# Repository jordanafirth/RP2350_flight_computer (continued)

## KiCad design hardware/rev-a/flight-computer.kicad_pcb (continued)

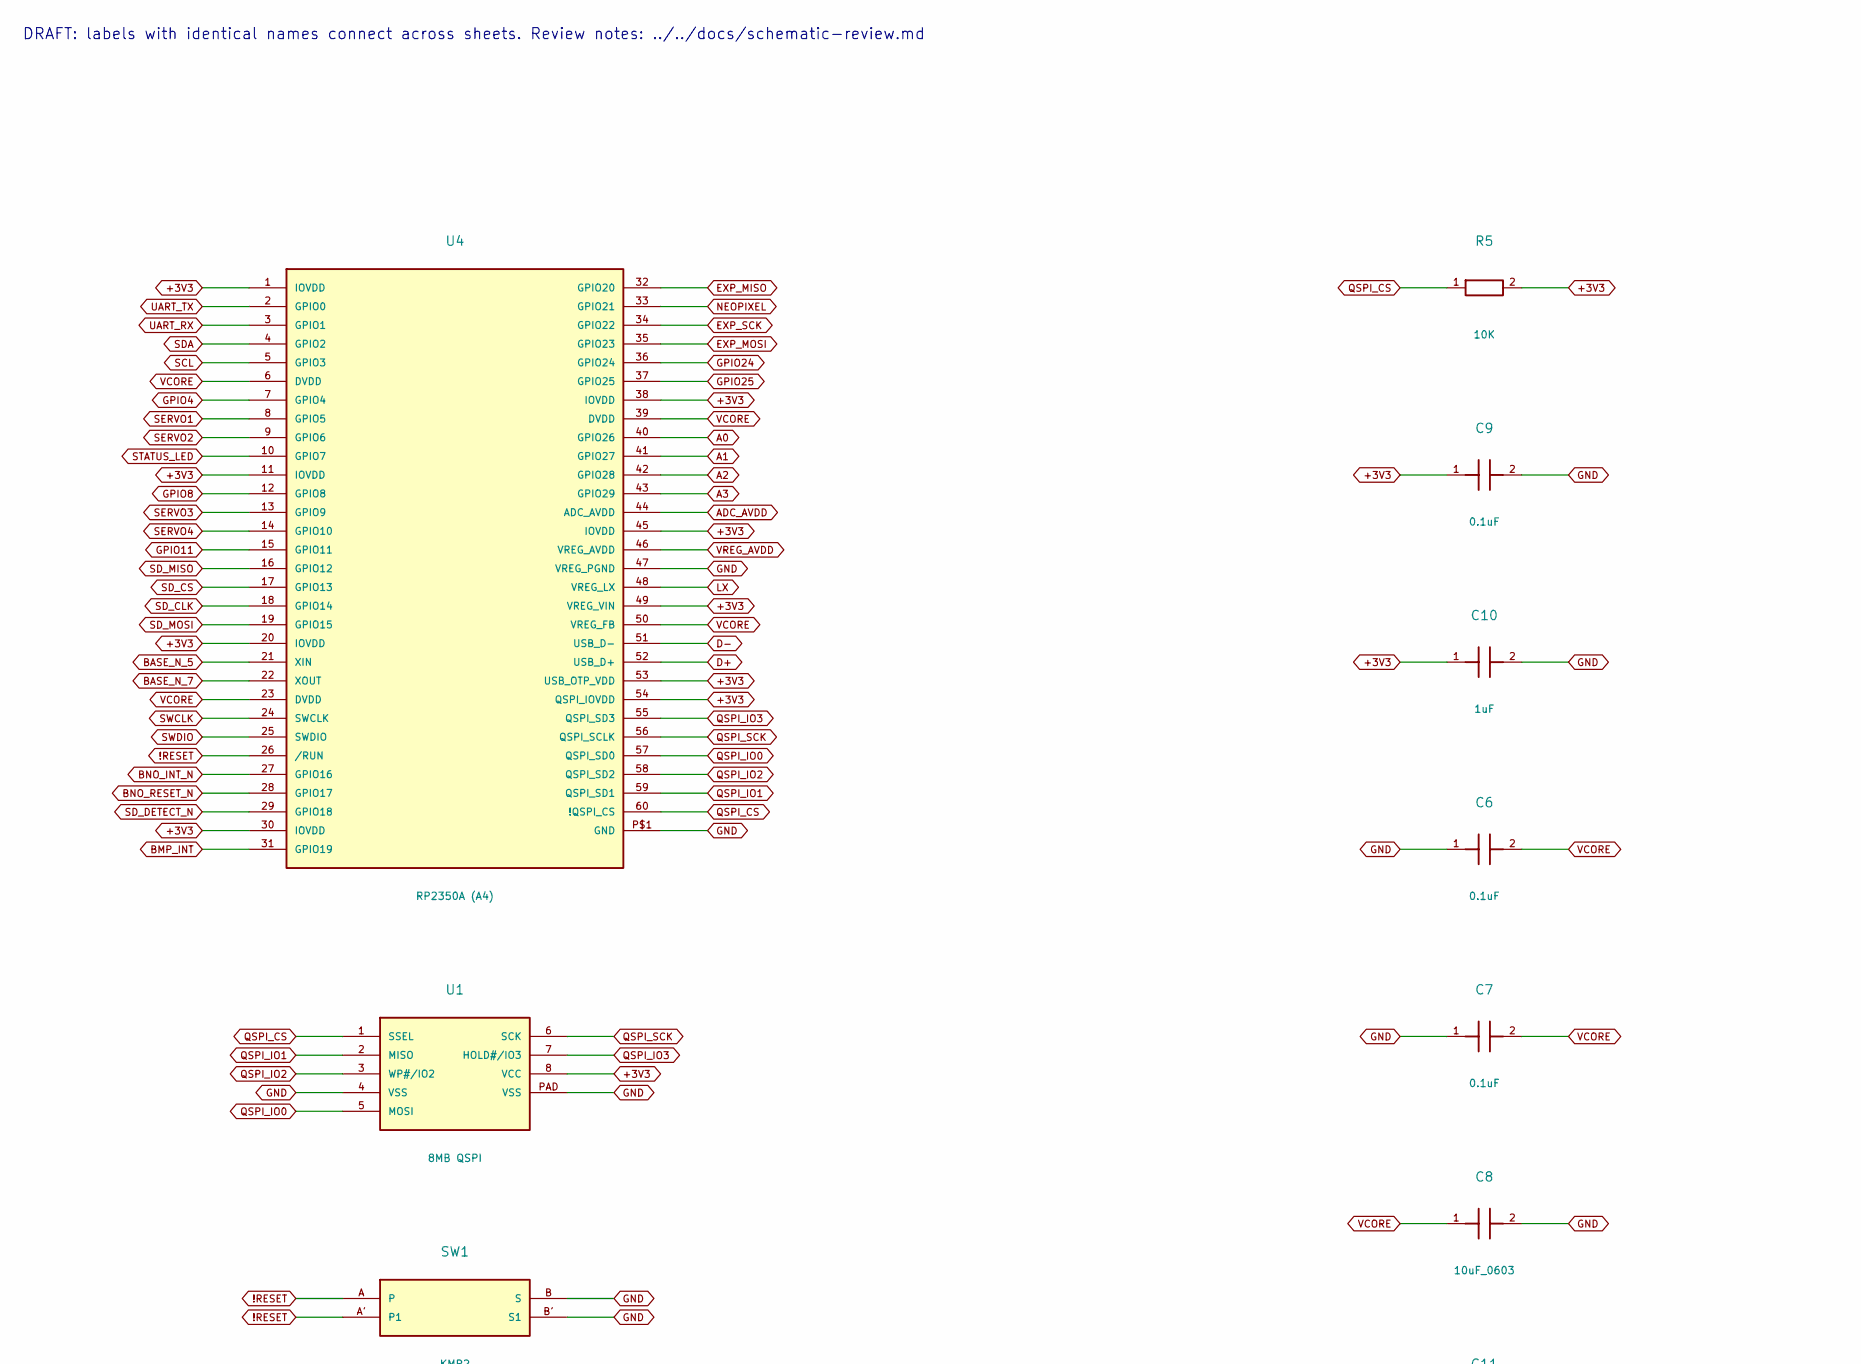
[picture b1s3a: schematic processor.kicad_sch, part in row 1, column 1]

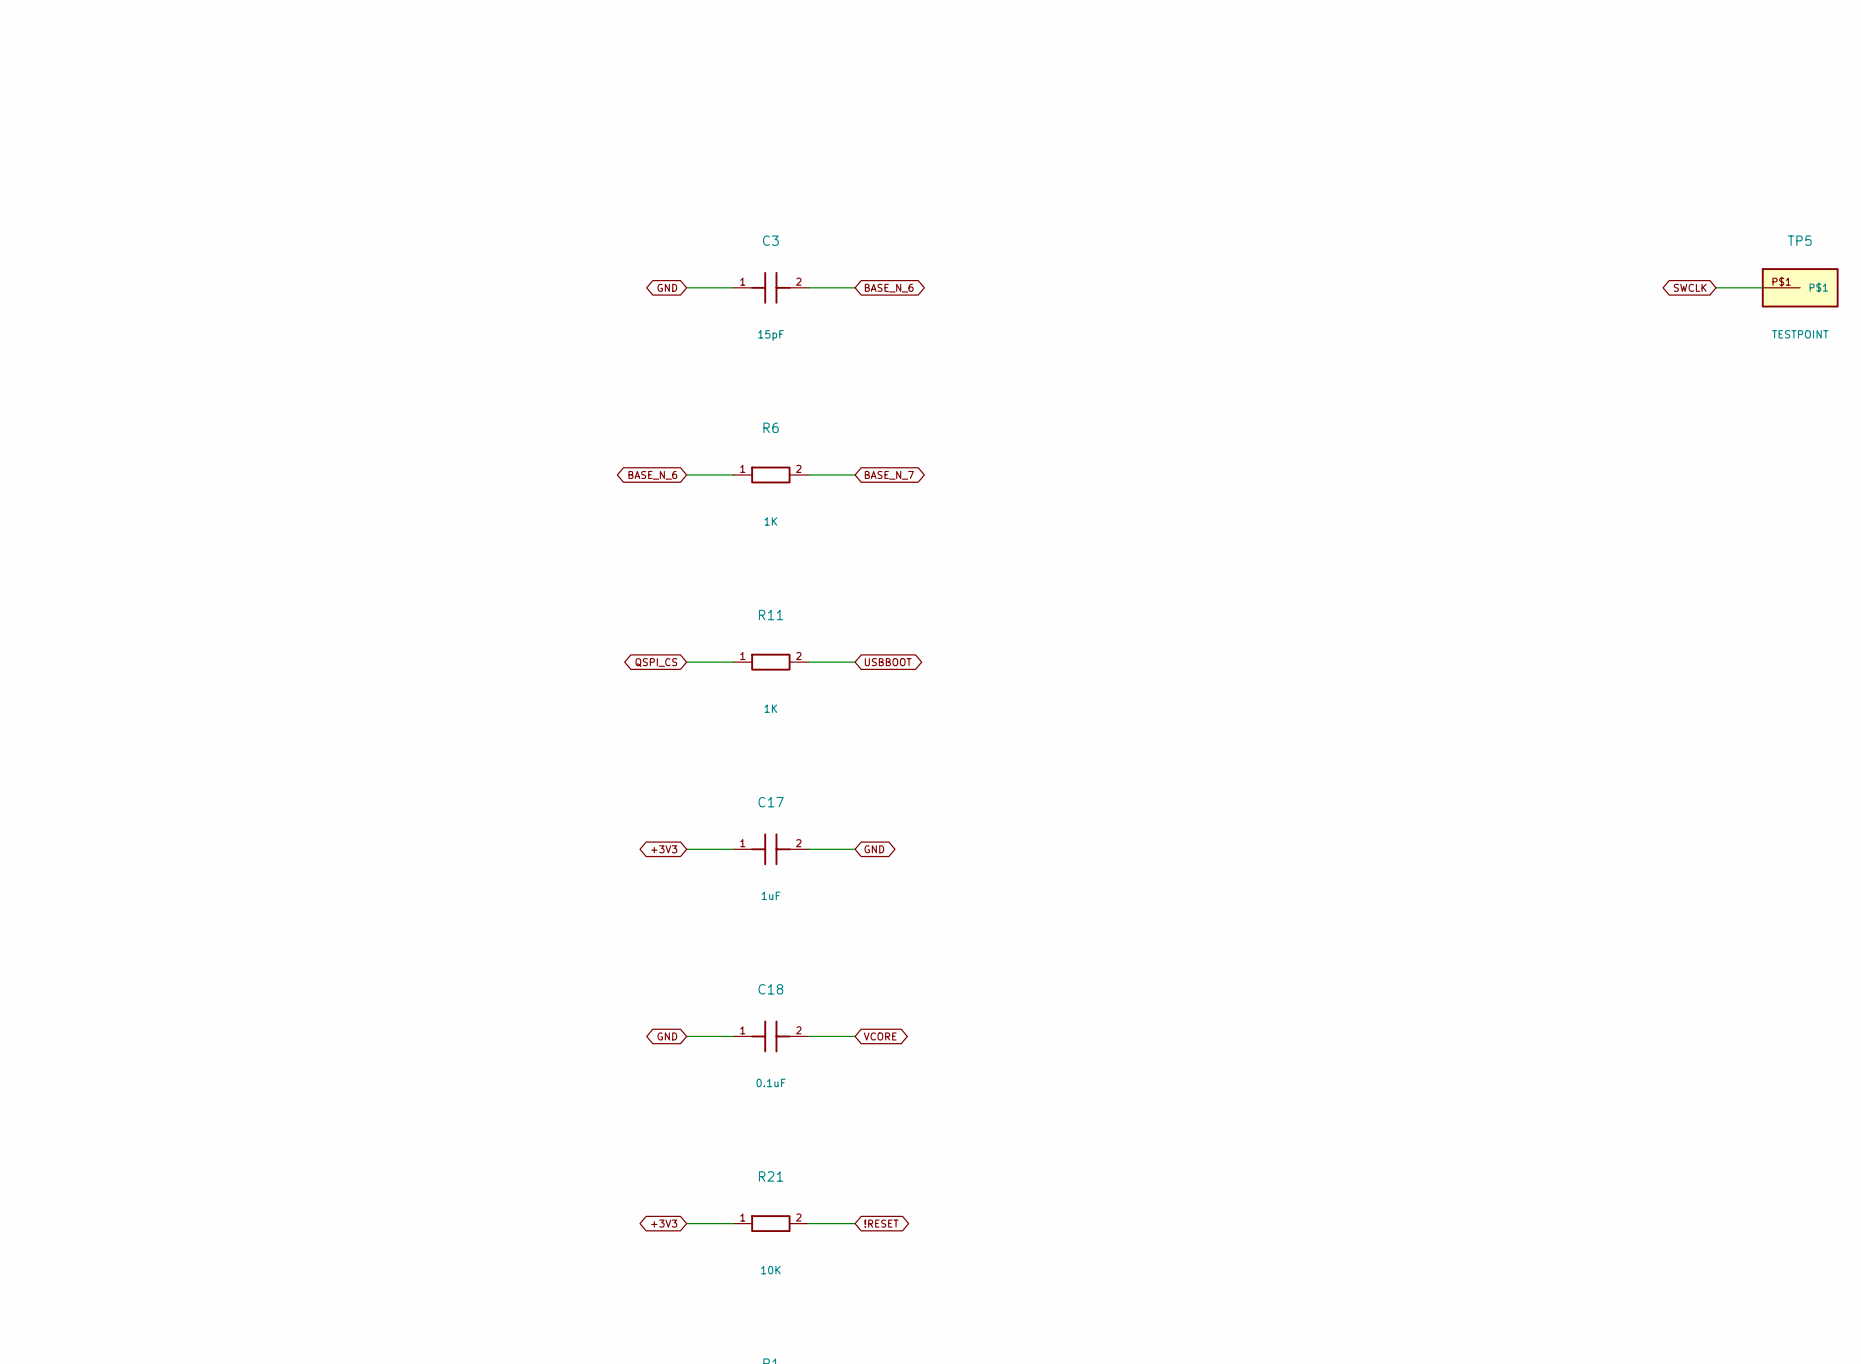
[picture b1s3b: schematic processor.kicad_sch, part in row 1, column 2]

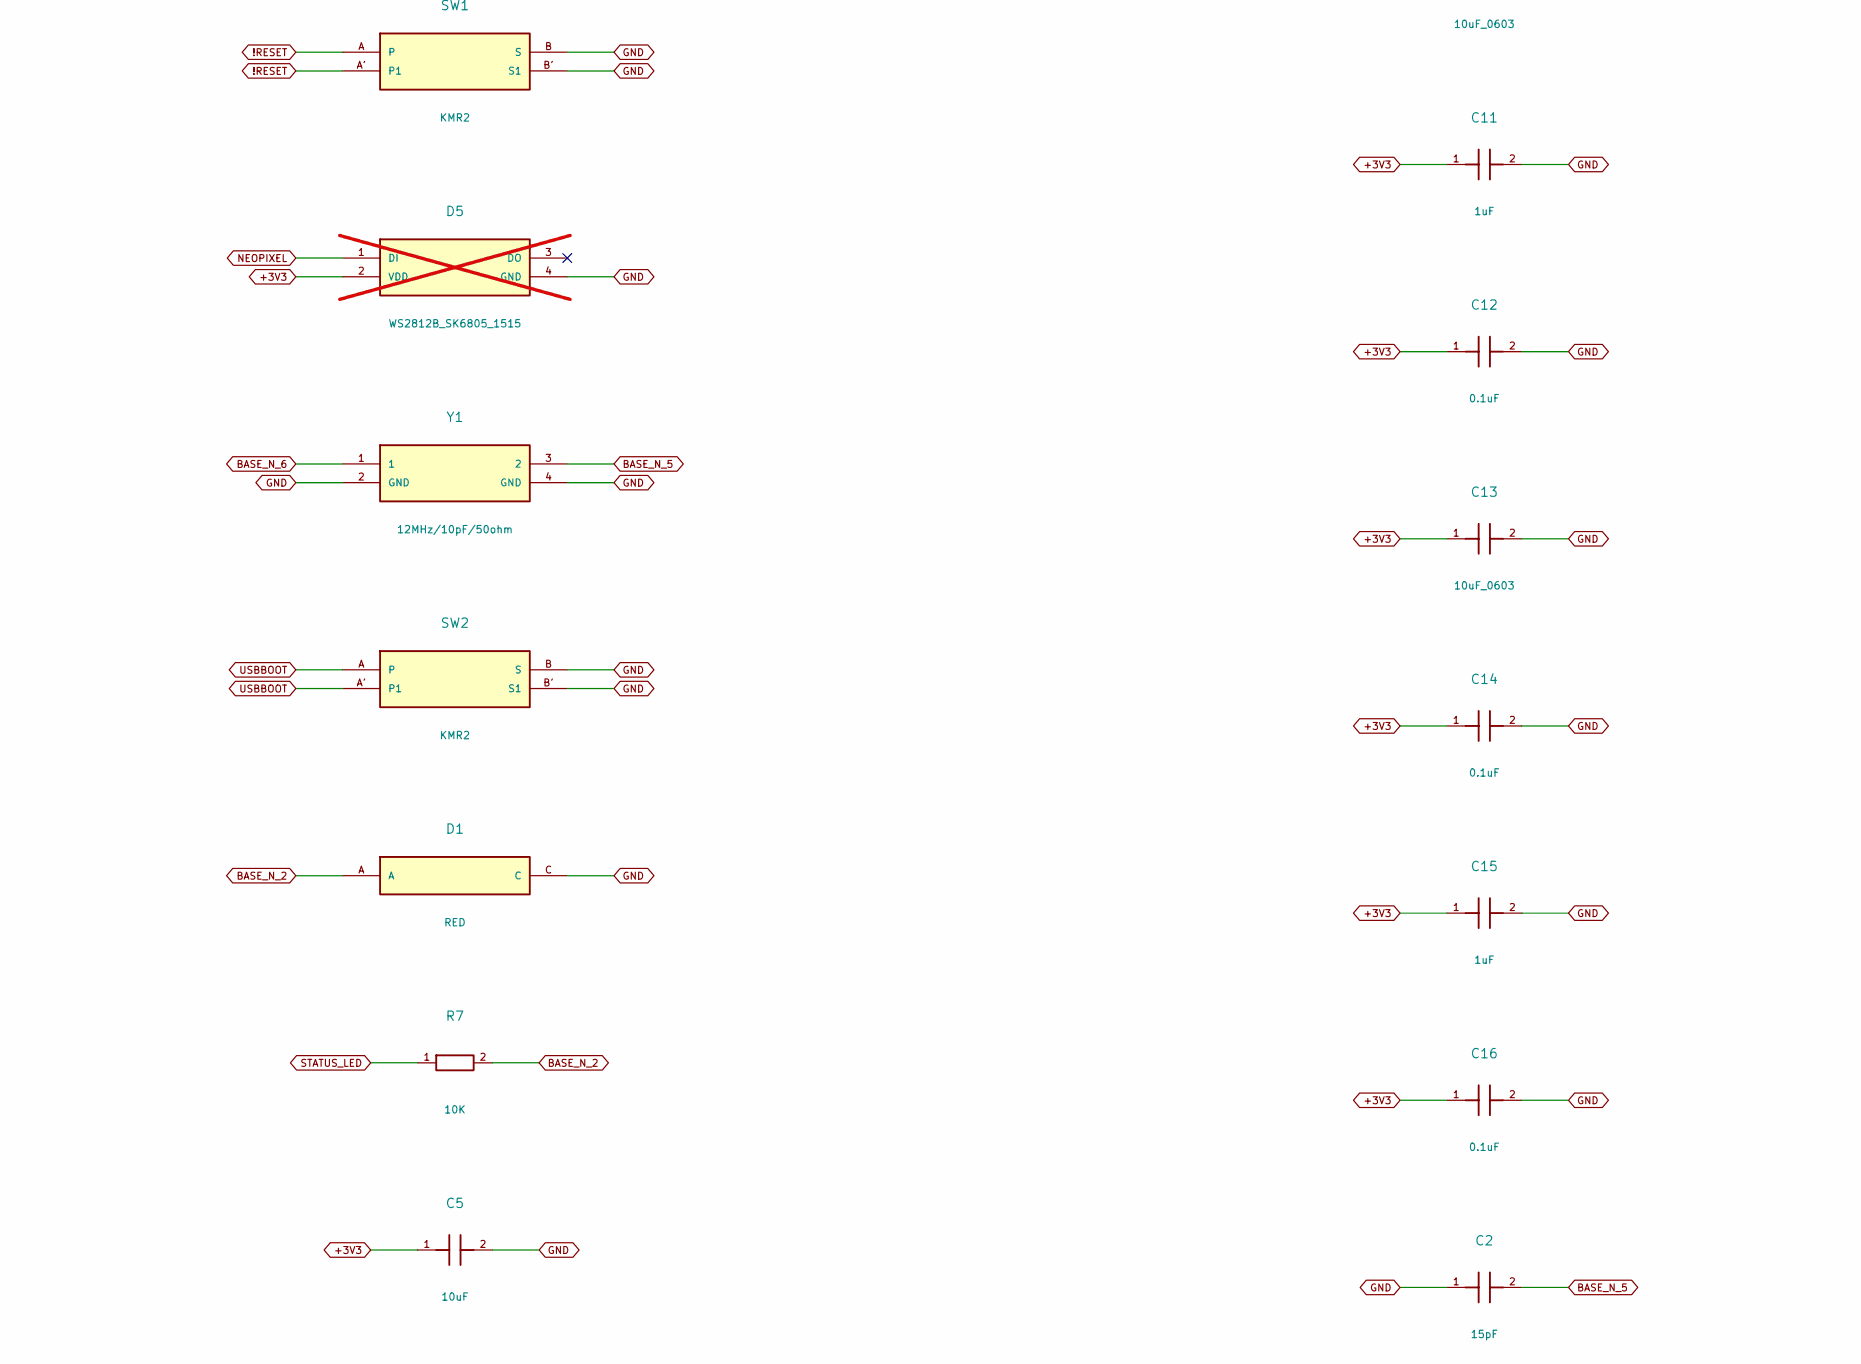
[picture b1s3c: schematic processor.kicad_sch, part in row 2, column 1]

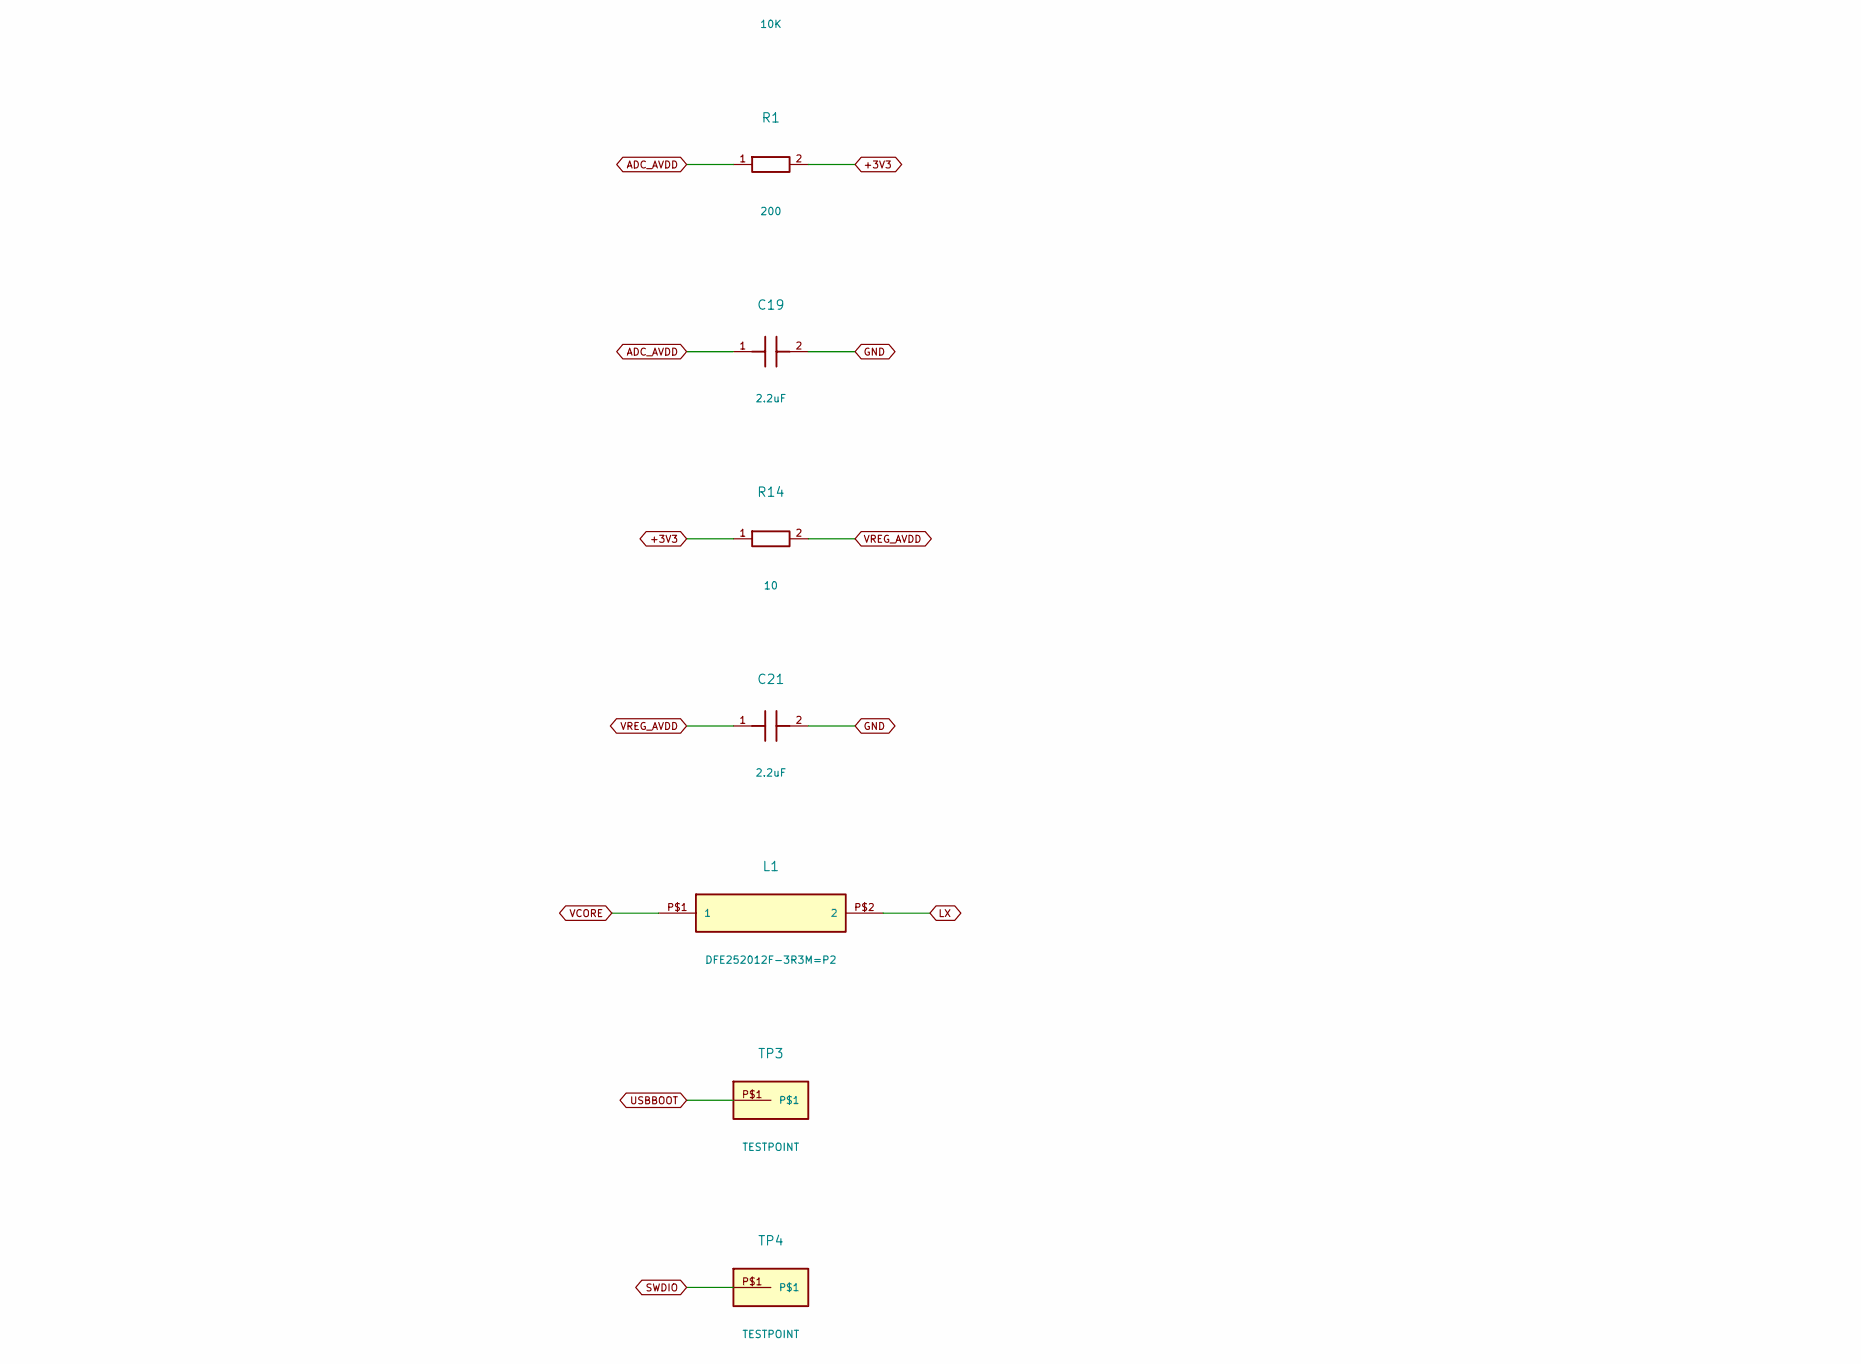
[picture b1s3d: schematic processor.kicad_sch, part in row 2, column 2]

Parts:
C2, C3: 15pF; _0402NO; MPN GRM1555C1H150JA01D
C5: 10uF; 0603-NO; MPN GRM188R60J106ME47D
C6, C7, C9, C12, C14, C16, C18: 0.1uF; _0402NO; MPN GRM155R71C104KA88D
C8, C13: 10uF_0603; _0603MP; MPN GRM188R60J106ME47D
C10, C11, C15, C17: 1uF; _0402NO; MPN GRM155R61A105KE15D
C19, C21: 2.2uF; _0402NO; MPN GRM155R61A225KE01D
D1: RED; CHIPLED_0603_NOOUTLINE; MPN LTST-C190KRKT
D5: WS2812B_SK6805_1515; SK6805_1515; MPN SK6805-EC15; not fitted
L1: DFE252012F-3R3M=P2; INDUCTOR_1007; MPN DFE252012F-3R3M=P2
R1: 200; _0402NO; MPN RC0402FR-07200RL
R5, R7, R21: 10K; _0402NO; MPN RC0402FR-0710KL
R6, R11: 1K; _0402NO; MPN RC0402FR-071KL
R14: 10; _0402NO; MPN RC0402FR-0710RL
SW1, SW2: KMR2; BTN_RKB2_4.6X2.8; MPN KMR221GLFS
TP3: TESTPOINT; TESTPOINT_ROUND_1.5MM_NO
TP4, TP5: TESTPOINT; TESTPOINT_ROUND_1MM
U1: 8MB QSPI; USON8_4X4; MPN W25Q64JVXGIQ
U4: RP2350A (A4); QFN60_7MM_REDUCEDEPAD; MPN SC1509-A4
Y1: 12MHz/10pF/50ohm; Crystal_SMD_3225-4Pin_3.2x2.5mm; MPN ABM8-272-T3

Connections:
!RESET: R21.2, SW1.A, SW1.A' (P1), U4.26 (/RUN); also elsewhere on the board
+3V3: C5.1, C9.1, C10.1, C11.1, C12.1, C13.1, C14.1, C15.1, C16.1, C17.1, D5.2 (VDD), R1.2, R5.2, R14.1, R21.1, U1.8 (VCC), U4.1 (IOVDD), U4.11 (IOVDD), U4.20 (IOVDD), U4.30 (IOVDD), U4.38 (IOVDD), U4.45 (IOVDD), U4.49 (VREG_VIN), U4.53 (USB_OTP_VDD), U4.54 (QSPI_IOVDD); also elsewhere on the board
A0: U4.40 (GPIO26); also elsewhere on the board
A1: U4.41 (GPIO27); also elsewhere on the board
A2: U4.42 (GPIO28); also elsewhere on the board
A3: U4.43 (GPIO29); also elsewhere on the board
ADC_AVDD: C19.1, R1.1, U4.44 (ADC_AVDD)
BASE_N_2: D1.A, R7.2
BASE_N_5: C2.2, U4.21 (XIN), Y1.3 (2)
BASE_N_6: C3.2, R6.1, Y1.1
BASE_N_7: R6.2, U4.22 (XOUT)
BMP_INT: U4.31 (GPIO19); also elsewhere on the board
BNO_INT_N: U4.27 (GPIO16); also elsewhere on the board
BNO_RESET_N: U4.28 (GPIO17); also elsewhere on the board
D+: U4.52 (USB_D+); also elsewhere on the board
D-: U4.51 (USB_D-); also elsewhere on the board
EXP_MISO: U4.32 (GPIO20); also elsewhere on the board
EXP_MOSI: U4.35 (GPIO23); also elsewhere on the board
EXP_SCK: U4.34 (GPIO22); also elsewhere on the board
GND: C2.1, C3.1, C5.2, C6.1, C7.1, C8.2, C9.2, C10.2, C11.2, C12.2, C13.2, C14.2, C15.2, C16.2, C17.2, C18.1, C19.2, C21.2, D1.C, D5.4 (GND), SW1.B (S), SW1.B' (S1), SW2.B (S), SW2.B' (S1), U1.4 (VSS), U1.PAD (VSS), U4.47 (VREG_PGND), U4.P$1 (GND), Y1.2 (GND), Y1.4 (GND); also elsewhere on the board
GPIO4: U4.7 (GPIO4); also elsewhere on the board
GPIO8: U4.12 (GPIO8); also elsewhere on the board
GPIO11: U4.15 (GPIO11); also elsewhere on the board
GPIO24: U4.36 (GPIO24); also elsewhere on the board
GPIO25: U4.37 (GPIO25); also elsewhere on the board
LX: L1.P$2 (2), U4.48 (VREG_LX)
NEOPIXEL: D5.1 (DI), U4.33 (GPIO21)
QSPI_CS: R5.1, R11.1, U1.1 (SSEL), U4.60 (!QSPI_CS)
QSPI_IO0: U1.5 (MOSI), U4.57 (QSPI_SD0)
QSPI_IO1: U1.2 (MISO), U4.59 (QSPI_SD1)
QSPI_IO2: U1.3 (WP#/IO2), U4.58 (QSPI_SD2)
QSPI_IO3: U1.7 (HOLD#/IO3), U4.55 (QSPI_SD3)
QSPI_SCK: U1.6 (SCK), U4.56 (QSPI_SCLK)
SCL: U4.5 (GPIO3); also elsewhere on the board
SDA: U4.4 (GPIO2); also elsewhere on the board
SD_CLK: U4.18 (GPIO14); also elsewhere on the board
SD_CS: U4.17 (GPIO13); also elsewhere on the board
SD_DETECT_N: U4.29 (GPIO18); also elsewhere on the board
SD_MISO: U4.16 (GPIO12); also elsewhere on the board
SD_MOSI: U4.19 (GPIO15); also elsewhere on the board
SERVO1: U4.8 (GPIO5); also elsewhere on the board
SERVO2: U4.9 (GPIO6); also elsewhere on the board
SERVO3: U4.13 (GPIO9); also elsewhere on the board
SERVO4: U4.14 (GPIO10); also elsewhere on the board
STATUS_LED: R7.1, U4.10 (GPIO7); also elsewhere on the board
SWCLK: TP5.P$1, U4.24 (SWCLK)
SWDIO: TP4.P$1, U4.25 (SWDIO)
UART_RX: U4.3 (GPIO1); also elsewhere on the board
UART_TX: U4.2 (GPIO0); also elsewhere on the board
USBBOOT: R11.2, SW2.A, SW2.A' (P1), TP3.P$1
VCORE: C6.2, C7.2, C8.1, C18.2, L1.P$1 (1), U4.6 (DVDD), U4.23 (DVDD), U4.39 (DVDD), U4.50 (VREG_FB)
VREG_AVDD: C21.1, R14.2, U4.46 (VREG_AVDD)

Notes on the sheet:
DRAFT: labels with identical names connect across sheets. Review notes: ../../docs/schematic-review.md

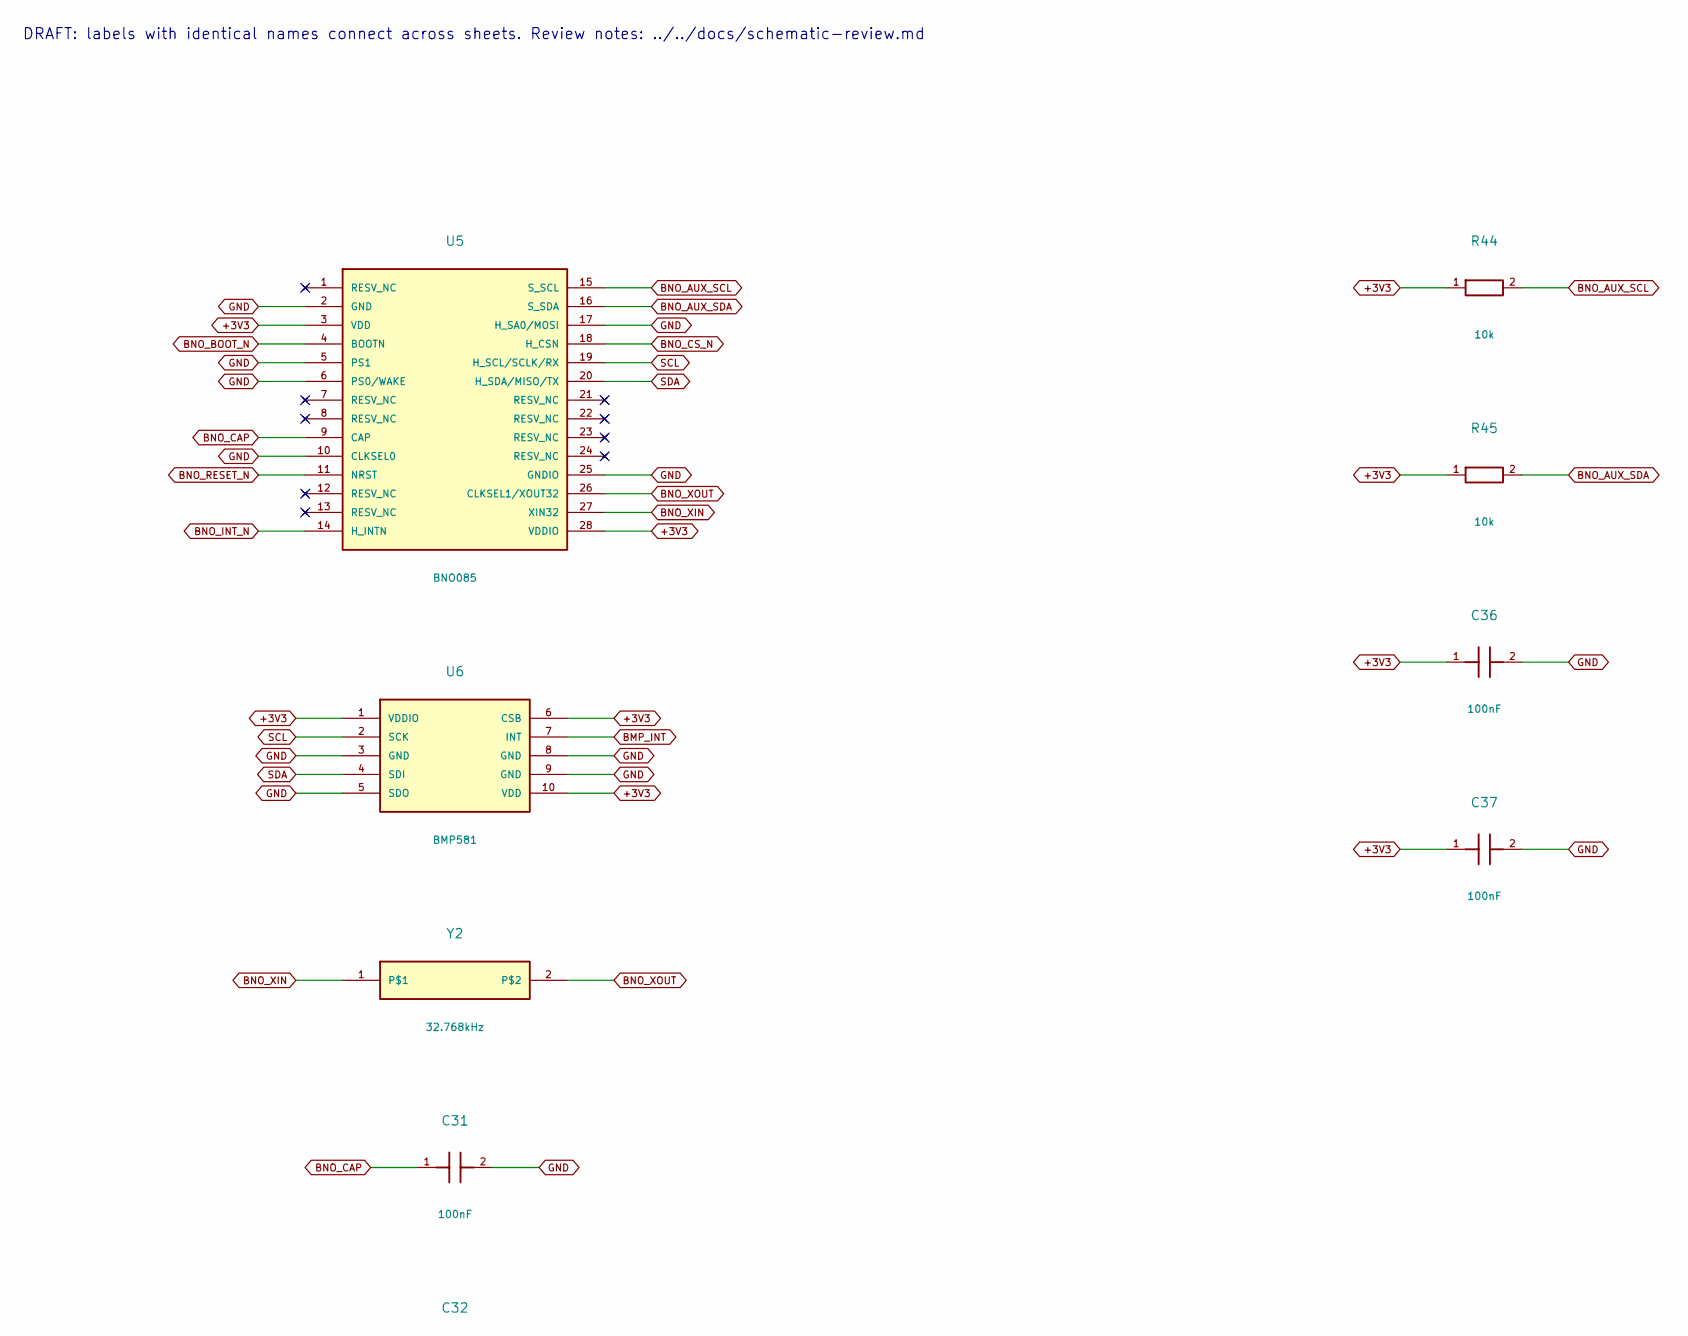
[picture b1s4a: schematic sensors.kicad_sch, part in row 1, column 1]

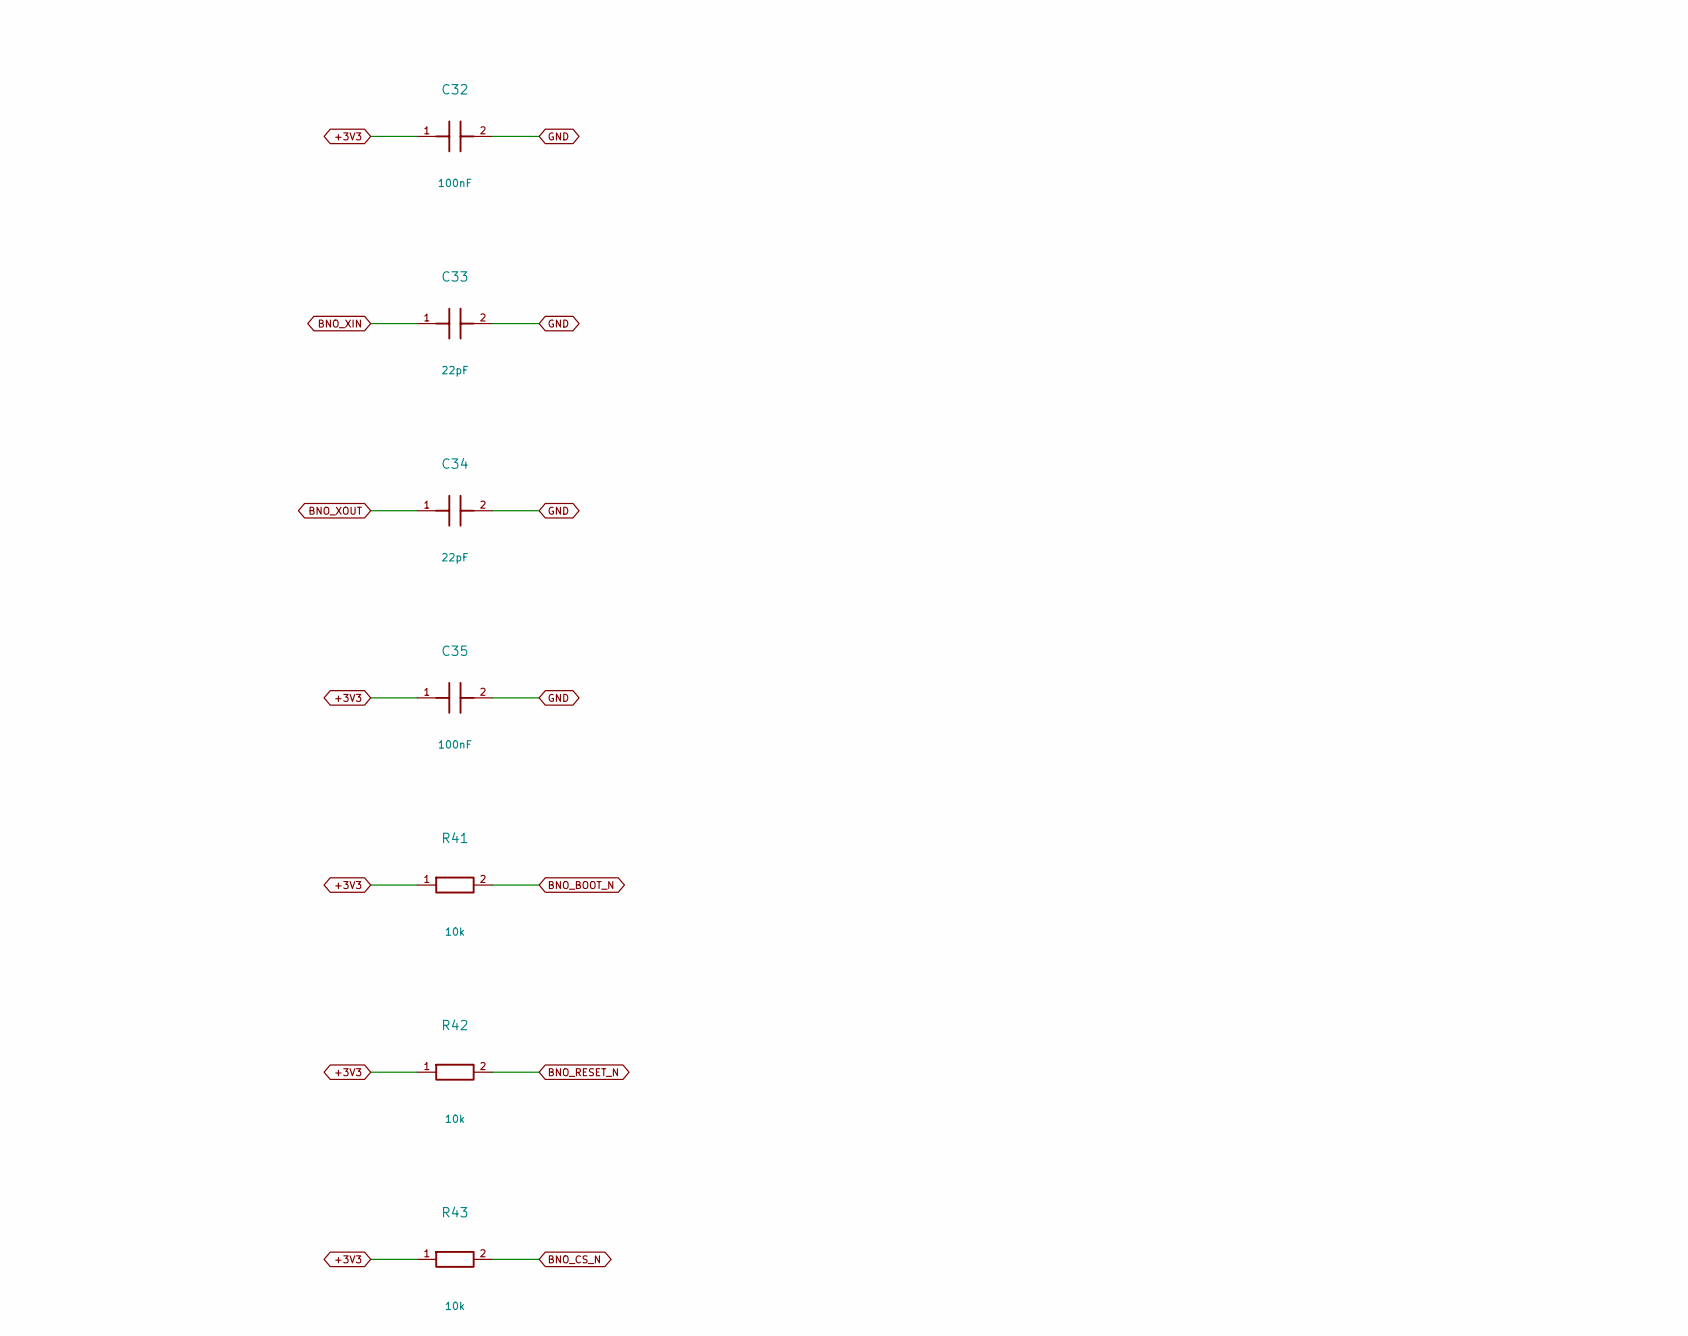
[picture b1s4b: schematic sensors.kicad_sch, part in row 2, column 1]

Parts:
C31, C32, C35, C36, C37: 100nF; C_0603_1608Metric; MPN GRM188R71H104KA93D
C33, C34: 22pF; C_0603_1608Metric; MPN GRM1885C1H220JA01D
R41, R42, R43, R44, R45: 10k; R_0603_1608Metric; MPN RC0603FR-0710KL
U5: BNO085; BNO080; MPN BNO085
U6: BMP581; BMP388; MPN BMP581
Y2: 32.768kHz; Crystal_SMD_3215-2Pin_3.2x1.5mm; MPN ABS07-32.768KHZ-T

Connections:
+3V3: C32.1, C35.1, C36.1, C37.1, R41.1, R42.1, R43.1, R44.1, R45.1, U5.3 (VDD), U5.28 (VDDIO), U6.1 (VDDIO), U6.6 (CSB), U6.10 (VDD); also elsewhere on the board
BMP_INT: U6.7 (INT); also elsewhere on the board
BNO_AUX_SCL: R44.2, U5.15 (S_SCL)
BNO_AUX_SDA: R45.2, U5.16 (S_SDA)
BNO_BOOT_N: R41.2, U5.4 (BOOTN)
BNO_CAP: C31.1, U5.9 (CAP)
BNO_CS_N: R43.2, U5.18 (H_CSN)
BNO_INT_N: U5.14 (H_INTN); also elsewhere on the board
BNO_RESET_N: R42.2, U5.11 (NRST); also elsewhere on the board
BNO_XIN: C33.1, U5.27 (XIN32), Y2.1
BNO_XOUT: C34.1, U5.26 (CLKSEL1/XOUT32), Y2.2
GND: C31.2, C32.2, C33.2, C34.2, C35.2, C36.2, C37.2, U5.2 (GND), U5.5 (PS1), U5.6 (PS0/WAKE), U5.10 (CLKSEL0), U5.17 (H_SA0/MOSI), U5.25 (GNDIO), U6.3 (GND), U6.5 (SDO), U6.8 (GND), U6.9 (GND); also elsewhere on the board
SCL: U5.19 (H_SCL/SCLK/RX), U6.2 (SCK); also elsewhere on the board
SDA: U5.20 (H_SDA/MISO/TX), U6.4 (SDI); also elsewhere on the board

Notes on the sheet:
DRAFT: labels with identical names connect across sheets. Review notes: ../../docs/schematic-review.md
